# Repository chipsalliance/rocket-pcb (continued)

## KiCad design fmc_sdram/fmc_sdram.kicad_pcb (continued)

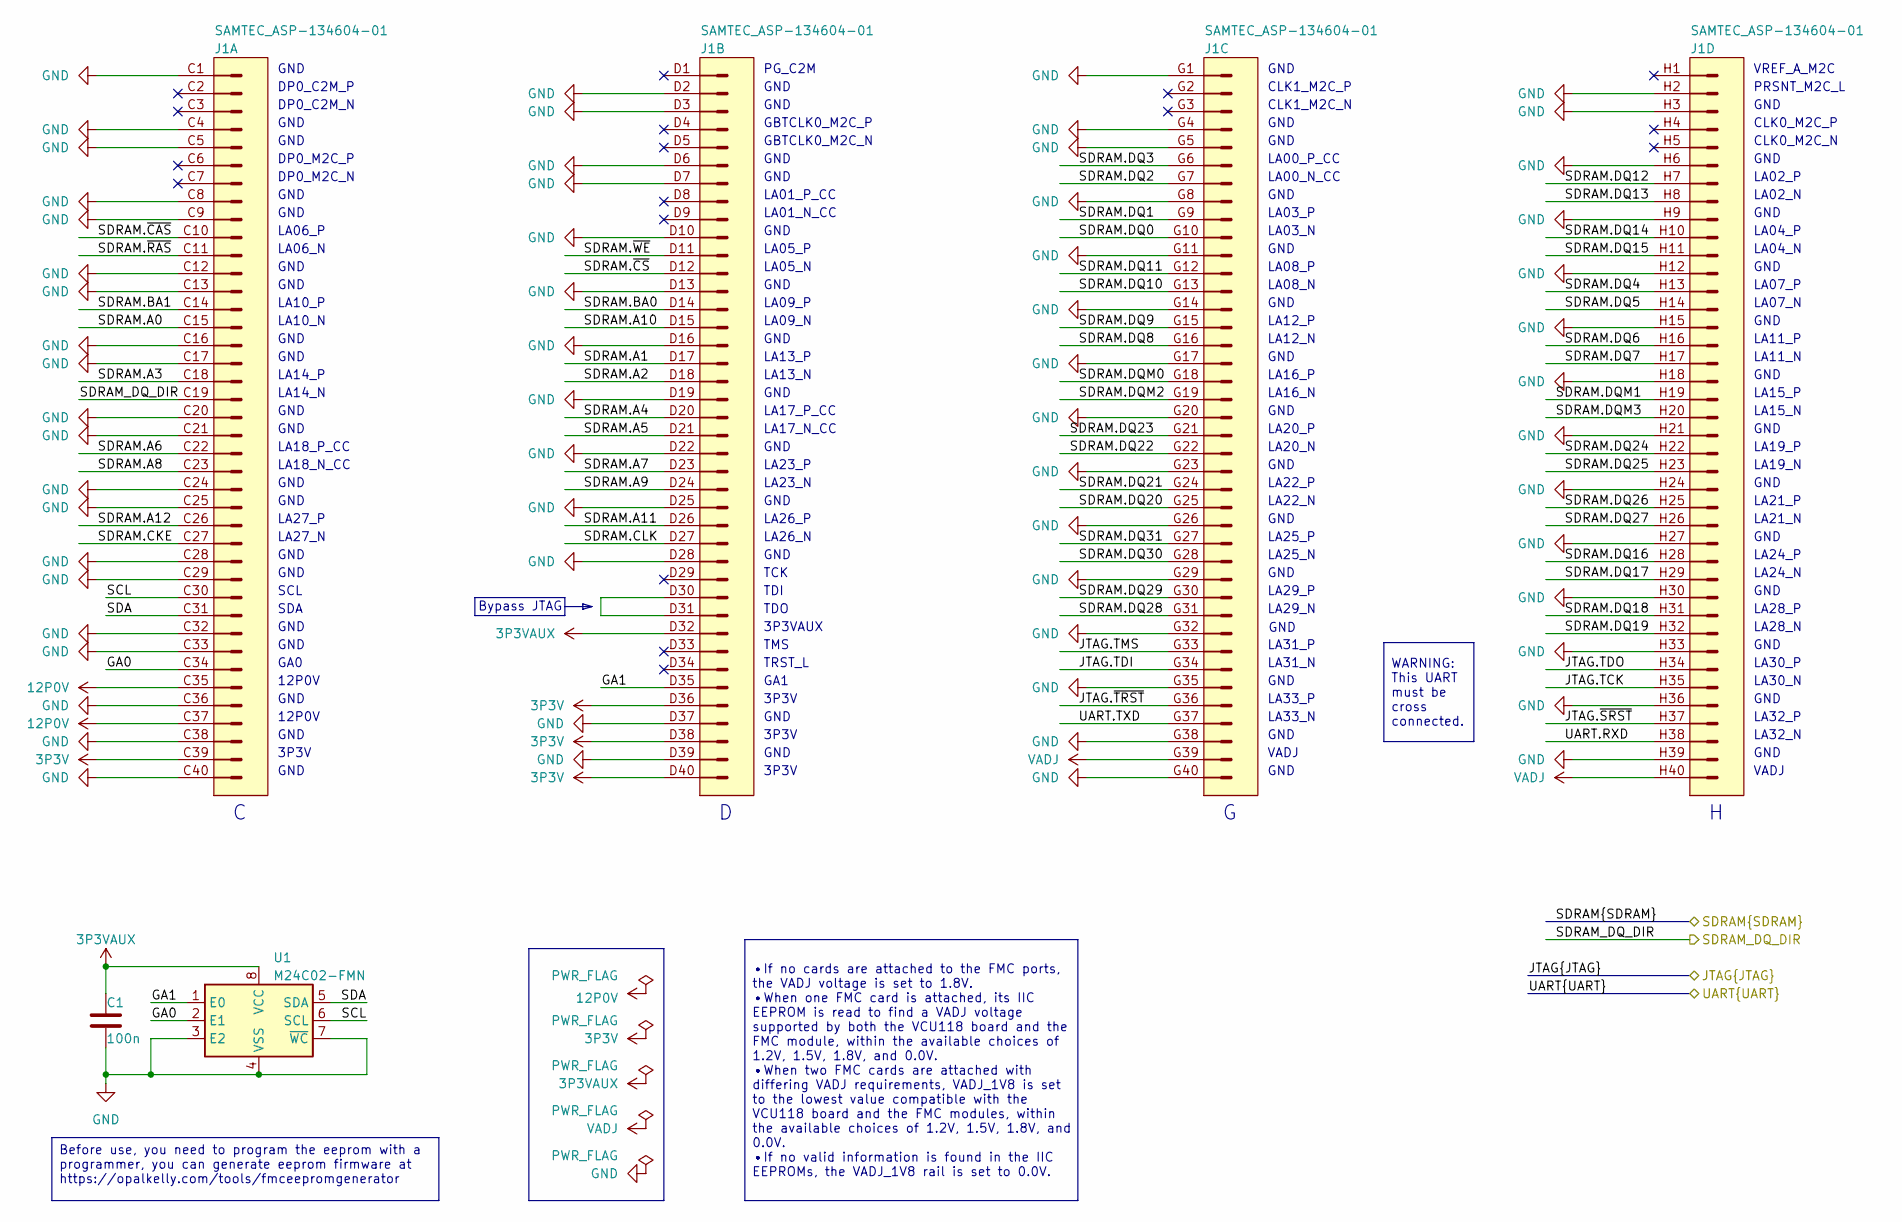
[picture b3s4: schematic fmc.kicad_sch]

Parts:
C1: 100n; C_0402_1005Metric
J1: SAMTEC_ASP-134604-01; Samtec_FMC_ASP-134604-01_4x40_P1.27mm
U1: M24C02-FMN; SOIC-8_3.9x4.9mm_P1.27mm

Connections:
3P3V: J1.C39 (Pin_39), J1.D36 (d36), J1.D38 (d38), J1.D40 (d40); also elsewhere on the board
3P3VAUX: C1.1, J1.D32 (d32), U1.8 (VCC)
12P0V: J1.C35 (Pin_35), J1.C37 (Pin_37)
/FMC/GA0: J1.C34 (Pin_34), U1.2 (E1)
/FMC/GA1: J1.D35 (d35), U1.1 (E0)
/FMC/JTAG.TCK: J1.H35 (h35); also elsewhere on the board
/FMC/JTAG.TDI: J1.G34 (g34); also elsewhere on the board
/FMC/JTAG.TDO: J1.H34 (h34); also elsewhere on the board
/FMC/JTAG.TMS: J1.G33 (g33); also elsewhere on the board
/FMC/JTAG.~SRST: J1.H37 (h37); also elsewhere on the board
/FMC/JTAG.~TRST: J1.G36 (g36); also elsewhere on the board
/FMC/SCL: J1.C30 (Pin_30), U1.6 (SCL)
/FMC/SDA: J1.C31 (Pin_31), U1.5 (SDA)
/FMC/SDRAM.A0: J1.C15 (Pin_15); also elsewhere on the board
/FMC/SDRAM.A1: J1.D17 (d17); also elsewhere on the board
/FMC/SDRAM.A2: J1.D18 (d18); also elsewhere on the board
/FMC/SDRAM.A3: J1.C18 (Pin_18); also elsewhere on the board
/FMC/SDRAM.A4: J1.D20 (d20); also elsewhere on the board
/FMC/SDRAM.A5: J1.D21 (d21); also elsewhere on the board
/FMC/SDRAM.A6: J1.C22 (Pin_22); also elsewhere on the board
/FMC/SDRAM.A7: J1.D23 (d23); also elsewhere on the board
/FMC/SDRAM.A8: J1.C23 (Pin_23); also elsewhere on the board
/FMC/SDRAM.A9: J1.D24 (d24); also elsewhere on the board
/FMC/SDRAM.A10: J1.D15 (d15); also elsewhere on the board
/FMC/SDRAM.A11: J1.D26 (d26); also elsewhere on the board
/FMC/SDRAM.A12: J1.C26 (Pin_26); also elsewhere on the board
/FMC/SDRAM.BA0: J1.D14 (d14); also elsewhere on the board
/FMC/SDRAM.BA1: J1.C14 (Pin_14); also elsewhere on the board
/FMC/SDRAM.CKE: J1.C27 (Pin_27); also elsewhere on the board
/FMC/SDRAM.CLK: J1.D27 (d27); also elsewhere on the board
/FMC/SDRAM.DQ0: J1.G10 (g10); also elsewhere on the board
/FMC/SDRAM.DQ1: J1.G9 (g9); also elsewhere on the board
/FMC/SDRAM.DQ2: J1.G7 (g7); also elsewhere on the board
/FMC/SDRAM.DQ3: J1.G6 (g6); also elsewhere on the board
/FMC/SDRAM.DQ4: J1.H13 (h13); also elsewhere on the board
/FMC/SDRAM.DQ5: J1.H14 (h14); also elsewhere on the board
/FMC/SDRAM.DQ6: J1.H16 (h16); also elsewhere on the board
/FMC/SDRAM.DQ7: J1.H17 (h17); also elsewhere on the board
/FMC/SDRAM.DQ8: J1.G16 (g16); also elsewhere on the board
/FMC/SDRAM.DQ9: J1.G15 (g15); also elsewhere on the board
/FMC/SDRAM.DQ10: J1.G13 (g13); also elsewhere on the board
/FMC/SDRAM.DQ11: J1.G12 (g12); also elsewhere on the board
/FMC/SDRAM.DQ12: J1.H7 (h7); also elsewhere on the board
/FMC/SDRAM.DQ13: J1.H8 (h8); also elsewhere on the board
/FMC/SDRAM.DQ14: J1.H10 (h10); also elsewhere on the board
/FMC/SDRAM.DQ15: J1.H11 (h11); also elsewhere on the board
/FMC/SDRAM.DQ16: J1.H28 (h28); also elsewhere on the board
/FMC/SDRAM.DQ17: J1.H29 (h29); also elsewhere on the board
/FMC/SDRAM.DQ18: J1.H31 (h31); also elsewhere on the board
/FMC/SDRAM.DQ19: J1.H32 (h32); also elsewhere on the board
/FMC/SDRAM.DQ20: J1.G25 (g25); also elsewhere on the board
/FMC/SDRAM.DQ21: J1.G24 (g24); also elsewhere on the board
/FMC/SDRAM.DQ22: J1.G22 (g22); also elsewhere on the board
/FMC/SDRAM.DQ23: J1.G21 (g21); also elsewhere on the board
/FMC/SDRAM.DQ24: J1.H22 (h22); also elsewhere on the board
/FMC/SDRAM.DQ25: J1.H23 (h23); also elsewhere on the board
/FMC/SDRAM.DQ26: J1.H25 (h25); also elsewhere on the board
/FMC/SDRAM.DQ27: J1.H26 (h26); also elsewhere on the board
/FMC/SDRAM.DQ28: J1.G31 (g31); also elsewhere on the board
/FMC/SDRAM.DQ29: J1.G30 (g30); also elsewhere on the board
/FMC/SDRAM.DQ30: J1.G28 (g28); also elsewhere on the board
/FMC/SDRAM.DQ31: J1.G27 (g27); also elsewhere on the board
/FMC/SDRAM.DQM0: J1.G18 (g18); also elsewhere on the board
/FMC/SDRAM.DQM1: J1.H19 (h19); also elsewhere on the board
/FMC/SDRAM.DQM2: J1.G19 (g19); also elsewhere on the board
/FMC/SDRAM.DQM3: J1.H20 (h20); also elsewhere on the board
/FMC/SDRAM.~CAS: J1.C10 (Pin_10); also elsewhere on the board
/FMC/SDRAM.~CS: J1.D12 (d12); also elsewhere on the board
/FMC/SDRAM.~RAS: J1.C11 (Pin_11); also elsewhere on the board
/FMC/SDRAM.~WE: J1.D11 (d11); also elsewhere on the board
/FMC/SDRAM_DQ_DIR: J1.C19 (Pin_19); also elsewhere on the board
/FMC/UART.RXD: J1.H38 (h38); also elsewhere on the board
/FMC/UART.TXD: J1.G37 (g37); also elsewhere on the board
GND: C1.2, J1.C1 (Pin_1), J1.C4 (Pin_4), J1.C5 (Pin_5), J1.C8 (Pin_8), J1.C9 (Pin_9), J1.C12 (Pin_12), J1.C13 (Pin_13), J1.C16 (Pin_16), J1.C17 (Pin_17), J1.C20 (Pin_20), J1.C21 (Pin_21), J1.C24 (Pin_24), J1.C25 (Pin_25), J1.C28 (Pin_28), J1.C29 (Pin_29), J1.C32 (Pin_32), J1.C33 (Pin_33), J1.C36 (Pin_36), J1.C38 (Pin_38), J1.C40 (Pin_40), J1.D2 (d2), J1.D3 (d3), J1.D6 (d6), J1.D7 (d7), J1.D10 (d10), J1.D13 (d13), J1.D16 (d16), J1.D19 (d19), J1.D22 (d22), J1.D25 (d25), J1.D28 (d28), J1.D37 (d37), J1.D39 (d39), J1.G1 (g1), J1.G4 (g4), J1.G5 (g5), J1.G8 (g8), J1.G11 (g11), J1.G14 (g14), J1.G17 (g17), J1.G20 (g20), J1.G23 (g23), J1.G26 (g26), J1.G29 (g29), J1.G32 (g32), J1.G35 (g35), J1.G38 (g38), J1.G40 (g40), J1.H2 (h2), J1.H3 (h3), J1.H6 (h6), J1.H9 (h9), J1.H12 (h12), J1.H15 (h15), J1.H18 (h18), J1.H21 (h21), J1.H24 (h24), J1.H27 (h27), J1.H30 (h30), J1.H33 (h33), J1.H36 (h36), J1.H39 (h39), U1.3 (E2), U1.4 (VSS), U1.7 (~WC); also elsewhere on the board
unnamed: J1.D30 (d30), J1.D31 (d31)
VADJ: J1.G39 (g39), J1.H40 (h40); also elsewhere on the board

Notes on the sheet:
DP0_C2M_P
GND
GBTCLK0_M2C_P
LA18_N_CC
LA07_P
12P0V
LA23_N
LA29_P
LA14_N
LA03_N
LA23_P
3P3V
LA20_P
LA22_P
LA21_N
LA12_P
CLK0_M2C_N
LA15_P
LA30_N
LA01_N_CC
SDA
LA14_P
LA19_N
LA03_P
LA01_P_CC
SCL
VADJ
LA18_P_CC
GA0
LA05_P
LA25_P
PRSNT_M2C_L
LA12_N
LA10_N
LA04_N
TCK
DP0_M2C_P
CLK1_M2C_N
LA06_N
LA15_N

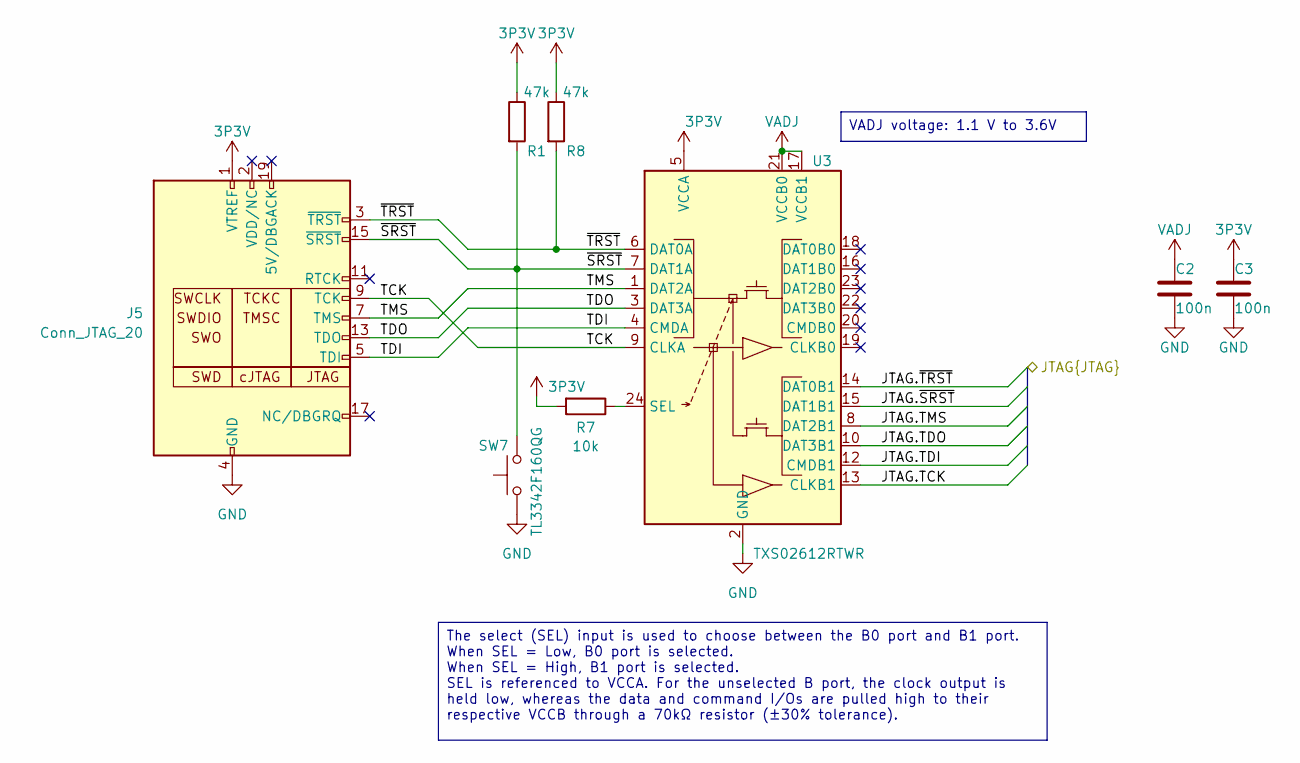
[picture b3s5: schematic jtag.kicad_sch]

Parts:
C2, C3: 100n; C_0402_1005Metric
J5: Conn_JTAG_20; IDC-Header_2x10_P2.54mm_Vertical_SMD
R1, R8: 47k; R_0402_1005Metric
R7: 10k; R_0402_1005Metric
SW7: TL3342F160QG; SW_SPST_TL3342
U3: TXS02612RTWR; WQFN-24-1EP_4x4mm_P0.5mm_EP2.45x2.45mm

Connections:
3P3V: C3.1, J5.1 (VTREF), R1.1, R7.2, R8.1, U3.5 (VCCA); also elsewhere on the board
/FMC/JTAG.TCK: U3.13 (CLKB1); also elsewhere on the board
/FMC/JTAG.TDI: U3.12 (CMDB1); also elsewhere on the board
/FMC/JTAG.TDO: U3.10 (DAT3B1); also elsewhere on the board
/FMC/JTAG.TMS: U3.8 (DAT2B1); also elsewhere on the board
/FMC/JTAG.~SRST: U3.15 (DAT1B1); also elsewhere on the board
/FMC/JTAG.~TRST: U3.14 (DAT0B1); also elsewhere on the board
/JTAG/TCK: J5.9 (TCK), U3.9 (CLKA)
/JTAG/TDI: J5.5 (TDI), U3.4 (CMDA)
/JTAG/TDO: J5.13 (TDO), U3.3 (DAT3A)
/JTAG/TMS: J5.7 (TMS), U3.1 (DAT2A)
/JTAG/~SRST: J5.15 (~SRST), R1.2, SW7.2, U3.7 (DAT1A)
/JTAG/~TRST: J5.3 (~TRST), R8.2, U3.6 (DAT0A)
GND: C2.2, C3.2, J5.4 (GND), J5.6 (GND), J5.8 (GND), J5.10 (GND), J5.12 (GND), J5.14 (GND), J5.16 (GND), J5.18 (GND), J5.20 (GND), SW7.1, U3.2 (GND), U3.11 (GND), U3.25 (GND); also elsewhere on the board
unnamed: R7.1, U3.24 (SEL)
VADJ: C2.1, U3.17 (VCCB1), U3.21 (VCCB0); also elsewhere on the board

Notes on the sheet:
VADJ voltage: 1.1 V to 3.6V
The select (SEL) input is used to choose between the B0 port and B1 port. When SEL = Low, B0 port is selected. When SEL = High, B1 port is selected. SEL is referenced to VCCA. For the unselected B port, the clock output is held low, whereas the data and command I/Os are pulled high to their respect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

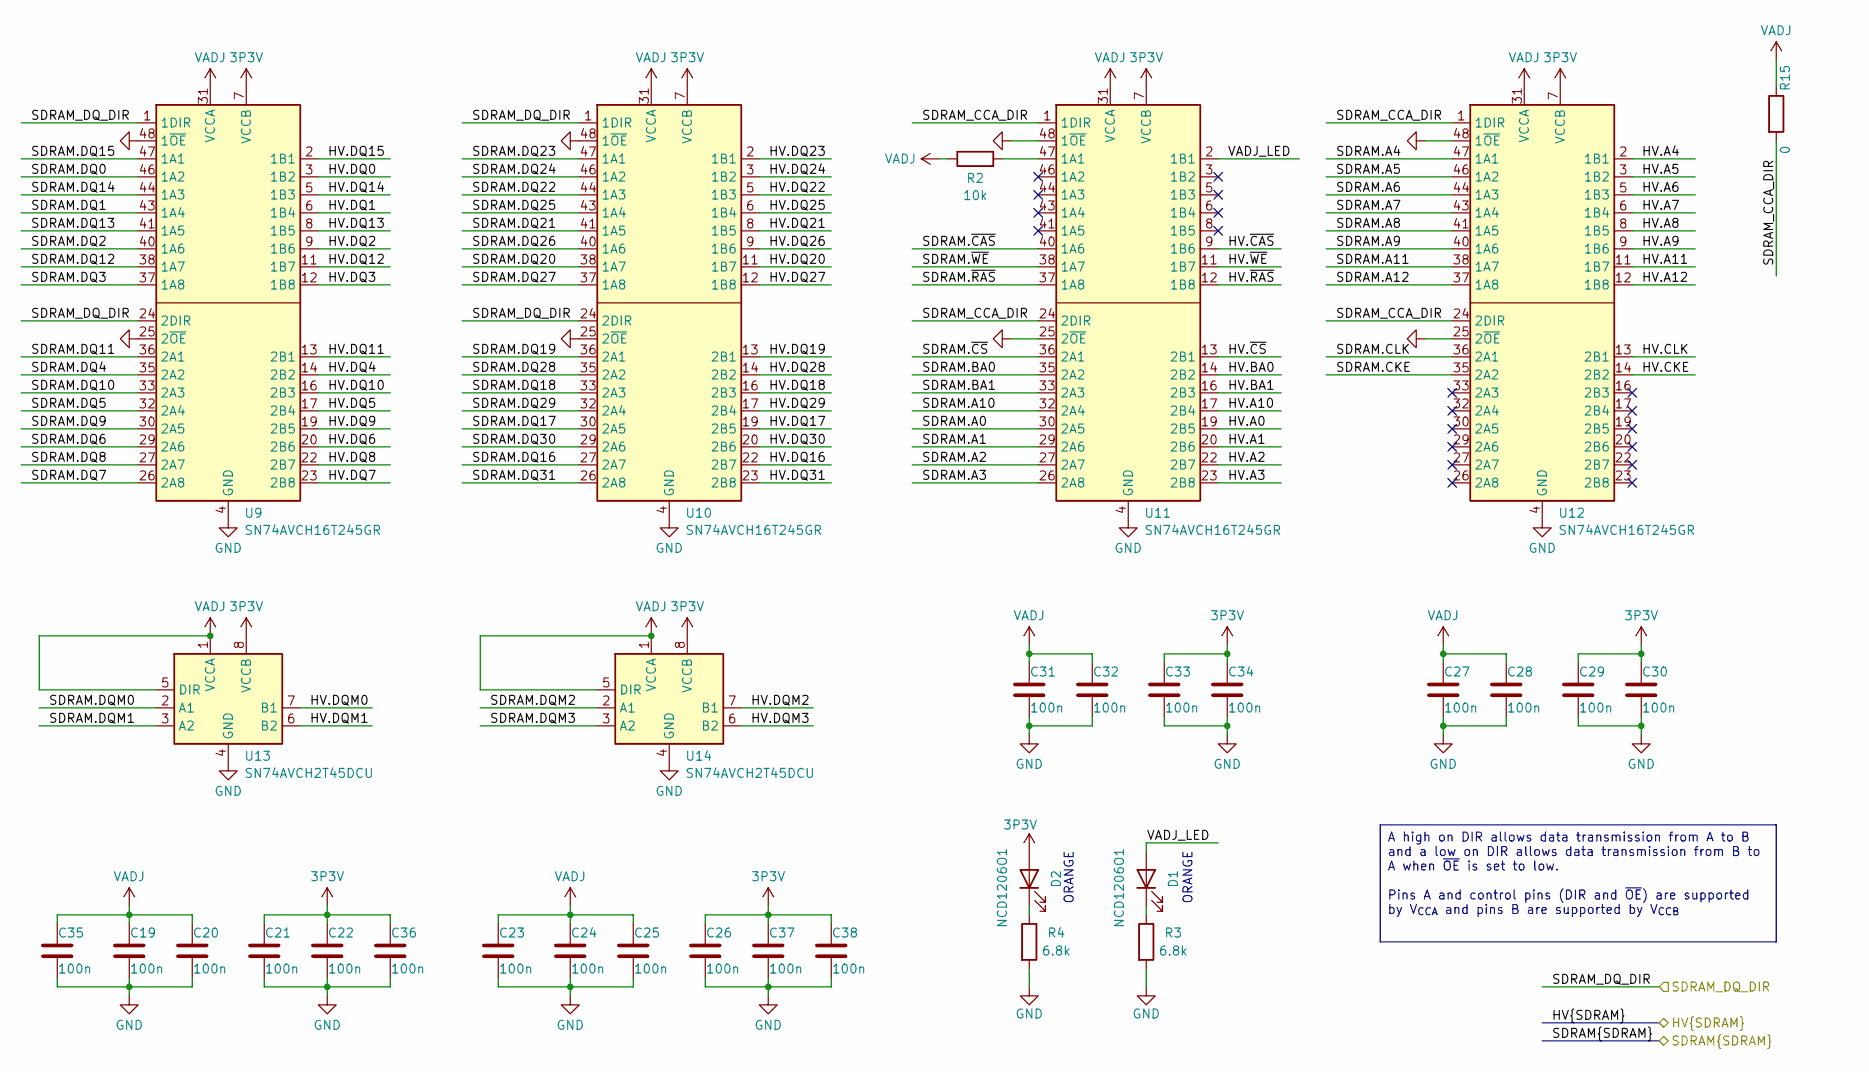
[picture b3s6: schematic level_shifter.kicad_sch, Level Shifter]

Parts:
C19, C20, C21, C22, C23, C24, C25, C26, C27, C28, C29, C30, C31, C32, C33, C34, C35, C36, C37, C38: 100n; C_0402_1005Metric
D1, D2: NCD1206O1; LED_1206_3216Metric
R2: 10k; R_0402_1005Metric
R3, R4: 6.8k; R_0402_1005Metric
R15: 0; R_0402_1005Metric
U9, U10, U11, U12: SN74AVCH16T245GR; TSSOP-48_6.1x12.5mm_P0.5mm
U13, U14: SN74AVCH2T45DCU; VSSOP-8_2.3x2mm_P0.5mm

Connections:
3P3V: C21.1, C22.1, C26.1, C29.1, C30.1, C33.1, C34.1, C36.1, C37.1, C38.1, D2.2 (A), U9.7 (VCCB), U9.18 (VCCB), U10.7 (VCCB), U10.18 (VCCB), U11.7 (VCCB), U11.18 (VCCB), U12.7 (VCCB), U12.18 (VCCB), U13.8 (VCCB), U14.8 (VCCB); also elsewhere on the board
/FMC/SDRAM.A0: U11.30 (2A5); also elsewhere on the board
/FMC/SDRAM.A1: U11.29 (2A6); also elsewhere on the board
/FMC/SDRAM.A2: U11.27 (2A7); also elsewhere on the board
/FMC/SDRAM.A3: U11.26 (2A8); also elsewhere on the board
/FMC/SDRAM.A4: U12.47 (1A1); also elsewhere on the board
/FMC/SDRAM.A5: U12.46 (1A2); also elsewhere on the board
/FMC/SDRAM.A6: U12.44 (1A3); also elsewhere on the board
/FMC/SDRAM.A7: U12.43 (1A4); also elsewhere on the board
/FMC/SDRAM.A8: U12.41 (1A5); also elsewhere on the board
/FMC/SDRAM.A9: U12.40 (1A6); also elsewhere on the board
/FMC/SDRAM.A10: U11.32 (2A4); also elsewhere on the board
/FMC/SDRAM.A11: U12.38 (1A7); also elsewhere on the board
/FMC/SDRAM.A12: U12.37 (1A8); also elsewhere on the board
/FMC/SDRAM.BA0: U11.35 (2A2); also elsewhere on the board
/FMC/SDRAM.BA1: U11.33 (2A3); also elsewhere on the board
/FMC/SDRAM.CKE: U12.35 (2A2); also elsewhere on the board
/FMC/SDRAM.CLK: U12.36 (2A1); also elsewhere on the board
/FMC/SDRAM.DQ0: U9.46 (1A2); also elsewhere on the board
/FMC/SDRAM.DQ1: U9.43 (1A4); also elsewhere on the board
/FMC/SDRAM.DQ2: U9.40 (1A6); also elsewhere on the board
/FMC/SDRAM.DQ3: U9.37 (1A8); also elsewhere on the board
/FMC/SDRAM.DQ4: U9.35 (2A2); also elsewhere on the board
/FMC/SDRAM.DQ5: U9.32 (2A4); also elsewhere on the board
/FMC/SDRAM.DQ6: U9.29 (2A6); also elsewhere on the board
/FMC/SDRAM.DQ7: U9.26 (2A8); also elsewhere on the board
/FMC/SDRAM.DQ8: U9.27 (2A7); also elsewhere on the board
/FMC/SDRAM.DQ9: U9.30 (2A5); also elsewhere on the board
/FMC/SDRAM.DQ10: U9.33 (2A3); also elsewhere on the board
/FMC/SDRAM.DQ11: U9.36 (2A1); also elsewhere on the board
/FMC/SDRAM.DQ12: U9.38 (1A7); also elsewhere on the board
/FMC/SDRAM.DQ13: U9.41 (1A5); also elsewhere on the board
/FMC/SDRAM.DQ14: U9.44 (1A3); also elsewhere on the board
/FMC/SDRAM.DQ15: U9.47 (1A1); also elsewhere on the board
/FMC/SDRAM.DQ16: U10.27 (2A7); also elsewhere on the board
/FMC/SDRAM.DQ17: U10.30 (2A5); also elsewhere on the board
/FMC/SDRAM.DQ18: U10.33 (2A3); also elsewhere on the board
/FMC/SDRAM.DQ19: U10.36 (2A1); also elsewhere on the board
/FMC/SDRAM.DQ20: U10.38 (1A7); also elsewhere on the board
/FMC/SDRAM.DQ21: U10.41 (1A5); also elsewhere on the board
/FMC/SDRAM.DQ22: U10.44 (1A3); also elsewhere on the board
/FMC/SDRAM.DQ23: U10.47 (1A1); also elsewhere on the board
/FMC/SDRAM.DQ24: U10.46 (1A2); also elsewhere on the board
/FMC/SDRAM.DQ25: U10.43 (1A4); also elsewhere on the board
/FMC/SDRAM.DQ26: U10.40 (1A6); also elsewhere on the board
/FMC/SDRAM.DQ27: U10.37 (1A8); also elsewhere on the board
/FMC/SDRAM.DQ28: U10.35 (2A2); also elsewhere on the board
/FMC/SDRAM.DQ29: U10.32 (2A4); also elsewhere on the board
/FMC/SDRAM.DQ30: U10.29 (2A6); also elsewhere on the board
/FMC/SDRAM.DQ31: U10.26 (2A8); also elsewhere on the board
/FMC/SDRAM.DQM0: U13.2 (A1); also elsewhere on the board
/FMC/SDRAM.DQM1: U13.3 (A2); also elsewhere on the board
/FMC/SDRAM.DQM2: U14.2 (A1); also elsewhere on the board
/FMC/SDRAM.DQM3: U14.3 (A2); also elsewhere on the board
/FMC/SDRAM.~CAS: U11.40 (1A6); also elsewhere on the board
/FMC/SDRAM.~CS: U11.36 (2A1); also elsewhere on the board
/FMC/SDRAM.~RAS: U11.37 (1A8); also elsewhere on the board
/FMC/SDRAM.~WE: U11.38 (1A7); also elsewhere on the board
/FMC/SDRAM_DQ_DIR: U9.1 (1DIR), U9.24 (2DIR), U10.1 (1DIR), U10.24 (2DIR); also elsewhere on the board
/Level Shifter/HV.A0: U11.19 (2B5); also elsewhere on the board
/Level Shifter/HV.A1: U11.20 (2B6); also elsewhere on the board
/Level Shifter/HV.A2: U11.22 (2B7); also elsewhere on the board
/Level Shifter/HV.A3: U11.23 (2B8); also elsewhere on the board
/Level Shifter/HV.A4: U12.2 (1B1); also elsewhere on the board
/Level Shifter/HV.A5: U12.3 (1B2); also elsewhere on the board
/Level Shifter/HV.A6: U12.5 (1B3); also elsewhere on the board
/Level Shifter/HV.A7: U12.6 (1B4); also elsewhere on the board
/Level Shifter/HV.A8: U12.8 (1B5); also elsewhere on the board
/Level Shifter/HV.A9: U12.9 (1B6); also elsewhere on the board
/Level Shifter/HV.A10: U11.17 (2B4); also elsewhere on the board
/Level Shifter/HV.A11: U12.11 (1B7); also elsewhere on the board
/Level Shifter/HV.A12: U12.12 (1B8); also elsewhere on the board
/Level Shifter/HV.BA0: U11.14 (2B2); also elsewhere on the board
/Level Shifter/HV.BA1: U11.16 (2B3); also elsewhere on the board
/Level Shifter/HV.CKE: U12.14 (2B2); also elsewhere on the board
/Level Shifter/HV.CLK: U12.13 (2B1); also elsewhere on the board
/Level Shifter/HV.DQ0: U9.3 (1B2); also elsewhere on the board
/Level Shifter/HV.DQ1: U9.6 (1B4); also elsewhere on the board
/Level Shifter/HV.DQ2: U9.9 (1B6); also elsewhere on the board
/Level Shifter/HV.DQ3: U9.12 (1B8); also elsewhere on the board
/Level Shifter/HV.DQ4: U9.14 (2B2); also elsewhere on the board
/Level Shifter/HV.DQ5: U9.17 (2B4); also elsewhere on the board
/Level Shifter/HV.DQ6: U9.20 (2B6); also elsewhere on the board
/Level Shifter/HV.DQ7: U9.23 (2B8); also elsewhere on the board
/Level Shifter/HV.DQ8: U9.22 (2B7); also elsewhere on the board
/Level Shifter/HV.DQ9: U9.19 (2B5); also elsewhere on the board
/Level Shifter/HV.DQ10: U9.16 (2B3); also elsewhere on the board
/Level Shifter/HV.DQ11: U9.13 (2B1); also elsewhere on the board
/Level Shifter/HV.DQ12: U9.11 (1B7); also elsewhere on the board
/Level Shifter/HV.DQ13: U9.8 (1B5); also elsewhere on the board
/Level Shifter/HV.DQ14: U9.5 (1B3); also elsewhere on the board
/Level Shifter/HV.DQ15: U9.2 (1B1); also elsewhere on the board
/Level Shifter/HV.DQ16: U10.22 (2B7); also elsewhere on the board
/Level Shifter/HV.DQ17: U10.19 (2B5); also elsewhere on the board
/Level Shifter/HV.DQ18: U10.16 (2B3); also elsewhere on the board
/Level Shifter/HV.DQ19: U10.13 (2B1); also elsewhere on the board
/Level Shifter/HV.DQ20: U10.11 (1B7); also elsewhere on the board
/Level Shifter/HV.DQ21: U10.8 (1B5); also elsewhere on the board
/Level Shifter/HV.DQ22: U10.5 (1B3); also elsewhere on the board
/Level Shifter/HV.DQ23: U10.2 (1B1); also elsewhere on the board
/Level Shifter/HV.DQ24: U10.3 (1B2); also elsewhere on the board
/Level Shifter/HV.DQ25: U10.6 (1B4); also elsewhere on the board
/Level Shifter/HV.DQ26: U10.9 (1B6); also elsewhere on the board
/Level Shifter/HV.DQ27: U10.12 (1B8); also elsewhere on the board
/Level Shifter/HV.DQ28: U10.14 (2B2); also elsewhere on the board
/Level Shifter/HV.DQ29: U10.17 (2B4); also elsewhere on the board
/Level Shifter/HV.DQ30: U10.20 (2B6); also elsewhere on the board
/Level Shifter/HV.DQ31: U10.23 (2B8); also elsewhere on the board
/Level Shifter/HV.DQM0: U13.7 (B1); also elsewhere on the board
/Level Shifter/HV.DQM1: U13.6 (B2); also elsewhere on the board
/Level Shifter/HV.DQM2: U14.7 (B1); also elsewhere on the board
/Level Shifter/HV.DQM3: U14.6 (B2); also elsewhere on the board
/Level Shifter/HV.~CAS: U11.9 (1B6); also elsewhere on the board
/Level Shifter/HV.~CS: U11.13 (2B1); also elsewhere on the board
/Level Shifter/HV.~RAS: U11.12 (1B8); also elsewhere on the board
/Level Shifter/HV.~WE: U11.11 (1B7); also elsewhere on the board
/Level Shifter/SDRAM_CCA_DIR: R15.2, U11.1 (1DIR), U11.24 (2DIR), U12.1 (1DIR), U12.24 (2DIR)
/Level Shifter/VADJ_LED: D1.2 (A), U11.2 (1B1)
GND: C19.2, C20.2, C21.2, C22.2, C23.2, C24.2, C25.2, C26.2, C27.2, C28.2, C29.2, C30.2, C31.2, C32.2, C33.2, C34.2, C35.2, C36.2, C37.2, C38.2, R3.2, R4.2, U9.4 (GND), U9.10 (GND), U9.15 (GND), U9.21 (GND), U9.25 (2~OE), U9.28 (GND), U9.34 (GND), U9.39 (GND), U9.45 (GND), U9.48 (1~OE), U10.4 (GND), U10.10 (GND), U10.15 (GND), U10.21 (GND), U10.25 (2~OE), U10.28 (GND), U10.34 (GND), U10.39 (GND), U10.45 (GND), U10.48 (1~OE), U11.4 (GND), U11.10 (GND), U11.15 (GND), U11.21 (GND), U11.25 (2~OE), U11.28 (GND), U11.34 (GND), U11.39 (GND), U11.45 (GND), U11.48 (1~OE), U12.4 (GND), U12.10 (GND), U12.15 (GND), U12.21 (GND), U12.25 (2~OE), U12.28 (GND), U12.34 (GND), U12.39 (GND), U12.45 (GND), U12.48 (1~OE), U13.4 (GND), U14.4 (GND); also elsewhere on the board
unnamed: D1.1 (K), R3.1
unnamed: D2.1 (K), R4.1
unnamed: R2.2, U11.47 (1A1)
VADJ: C19.1, C20.1, C23.1, C24.1, C25.1, C27.1, C28.1, C31.1, C32.1, C35.1, R2.1, R15.1, U9.31 (VCCA), U9.42 (VCCA), U10.31 (VCCA), U10.42 (VCCA), U11.31 (VCCA), U11.42 (VCCA), U12.31 (VCCA), U12.42 (VCCA), U13.1 (VCCA), U13.5 (DIR), U14.1 (VCCA), U14.5 (DIR); also elsewhere on the board

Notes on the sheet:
ORANGE
A high on DIR allows data transmission from A to B and a low on DIR allows data transmission from B to A when ~{OE} is set to low. Pins A and control pins (DIR and ~{OE}) are supported by V_{CCA} and pins B are supported by V_{CCB}

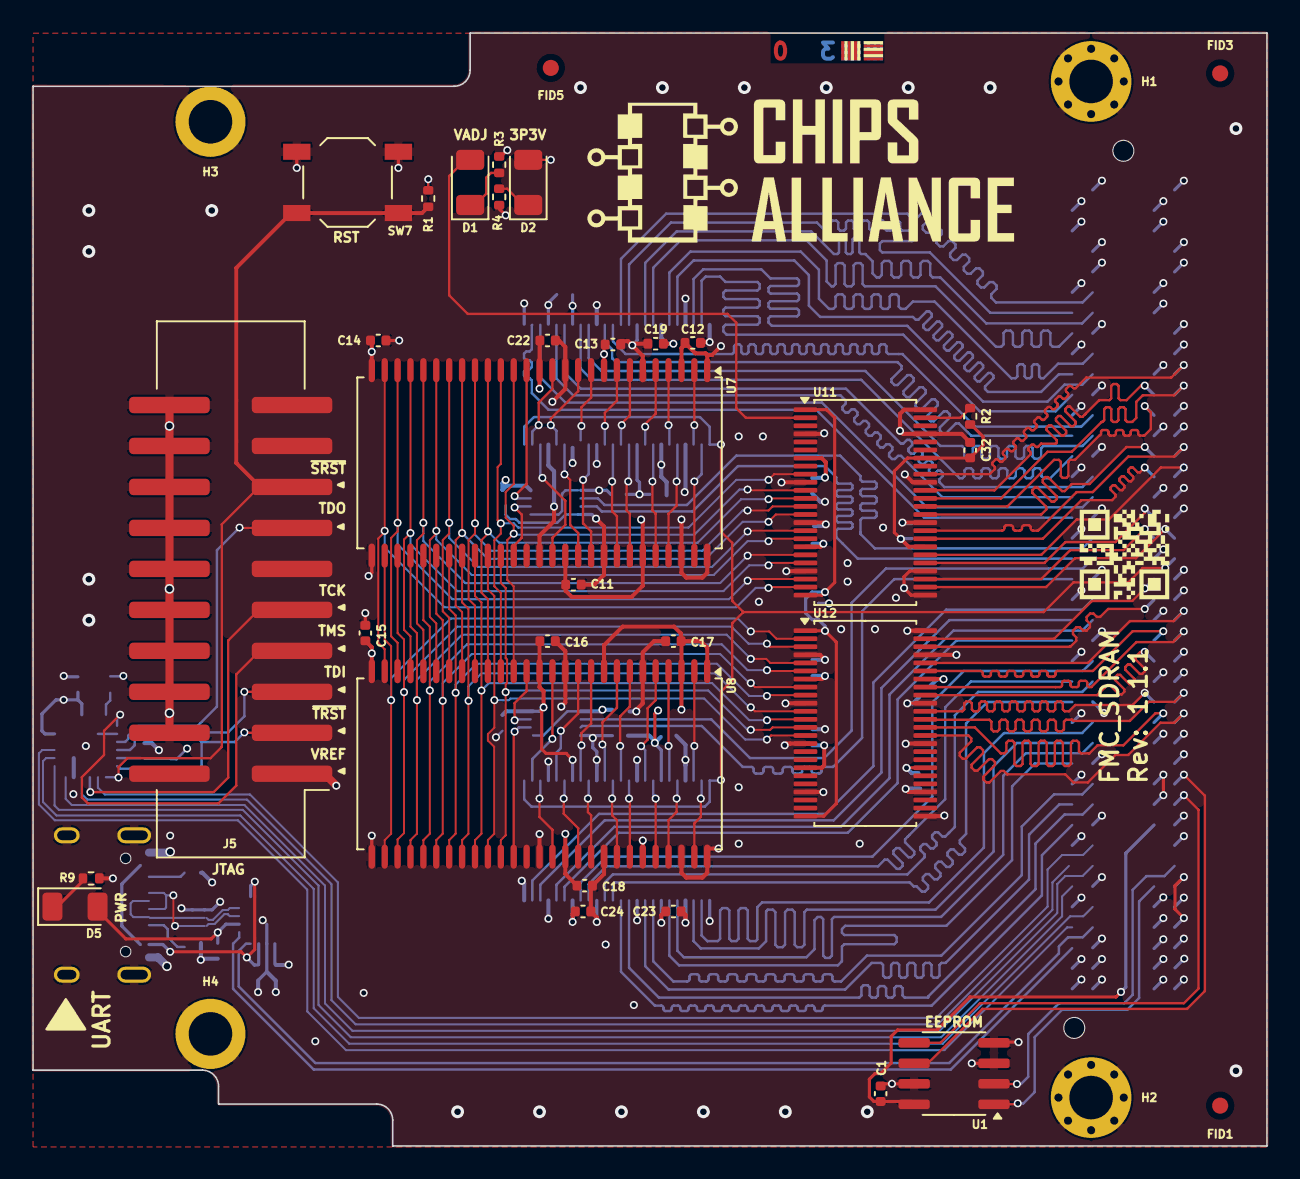
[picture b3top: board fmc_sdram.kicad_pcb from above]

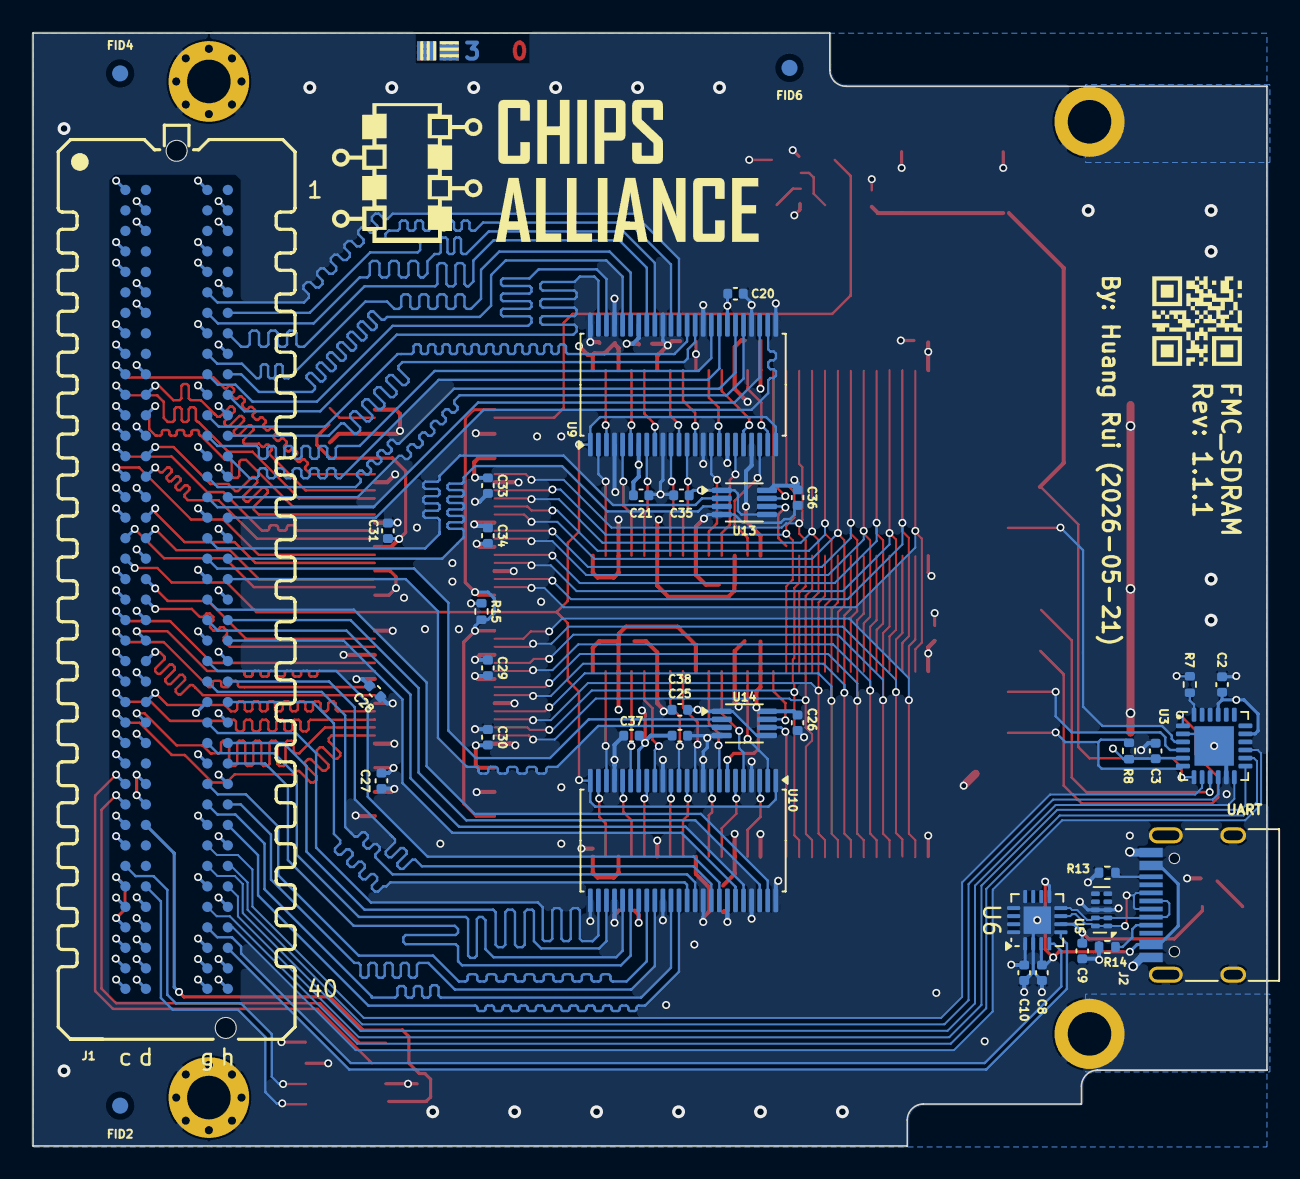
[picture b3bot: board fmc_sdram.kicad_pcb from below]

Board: 4 copper layers, 76.5 x 69.0 mm, 73 parts (37 on the bottom side), 152 nets.
